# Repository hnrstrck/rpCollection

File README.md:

# rpCollection
Java-Objekte zum Anfassen am Raspberry Pi

## Beschreibung
Bei der Objektorientierten Modellierung (OOM) spielen Objekte eine fundamentale Rolle. Der klassische Ansatz im Unterricht arbeitet mit rein virtuellen Objekten - sämtliche Interaktion und auch die Objektkommunikation spielt sich im Rechner ab. Nicht selten kommt es dabei vor, dass man Objekte im wahrsten Sinne des Wortes gar nicht "sieht".

Ziel dieses Projektes ist es, Objekte begreifbar zu machen und Objektkommunikation zu visualisieren. Dafür stehen für den Unterricht Bauteile bereit, mit denen sich verschiedene Szenarien modellieren lassen. Die Schülerinnen und Schüler bekommen so die Möglichkeit, Objekte tatsächlich anzufassen und ihren aktuellen State (Zustand) nicht nur über Methoden zu erfragen, sondern auch zu *sehen* (Bauteil: RGB-LED) oder zu *hören* (Bauteil: Summer).

Auch die Kommunikation ist dabei dabei zu verfolgen. Die Idee ist im folgenden Bild veranschaulicht (pinke Kreise = am Raspberry Pi angeschlossene Bauteile (über Steckbrett), pinke Pfeile = Objektkommunikation).

<div align="center">

</div>

Die Umsetzung im Unterricht setzt auf Groovy (genauer: die Groovy-Console, aufzurufen über `groovyConsole`), in der sich mit korrekter Java-Syntax mit den Objekten praktisch arbeiten lässt (Objekte erstelen, Objekte modifizieren, Methoden aufrufen, Attribute abfragen etc.).

Es stehen folgende Bauteile (bzw. Objekte) bereit:

* Diode (LED)
* RGB-LED
* Phototransistor
* Taster
* AD-Wandler (für den Anschluss eines MCP3008- / MCP3208-Chips)
* Summer
* Motor (für den Anschluss eines Fischertechnik-Motors)

### Bilder
Im folgenden Bild ist eine angeschlossene RGB-LED zu erkennen. Die Kabel für Rot, Grün und Blau sind farblich abgestimmt, Schwarz ist für Ground (GND).

<div align="center" style="margin-top:20px;margin-bottom:20px">

</div>

Bilder sind auch im Ornder

    /Arbeitsblaetter/img/

zu sehen (Anschluss eines Helligkeitssensors, Diode und einer RGB-LED). Weitere Bilder folgen bei Gelegenheit.

<table style="width:100%">
  <tr>
    <td>
    
    <div align="center">LED</div>
    </td>
    <td>
    
    <div align="center">RGB-LED</div>
    </td>
    <td>
    
    <div align="center">Taster</div>
    </td>
  </tr>
  <tr>
    <td>
    <div align="center">Phototransistor</div>
    </td>
    <td>
    <div align="center">Summer</div>
    </td>
    <td>
    <div align="center">AD-Wandler (mit vier Reglern)</div>
    </td>
  </tr>
</table>

## Voraussetzungen
### Hardware
* Raspberry Pi
* GPIO
* Steckbrett
* Kabel zum Anschluss des GPIO an den Raspberry Pi (Flachbandkabel)
* Bauteile (Bauanleitungen und Bilder folgen)

### Software
* Pi4J ([Website](http://pi4j.com))
* WiringPi ([Website](http://wiringpi.com/))
* Groovy ([Website](http://groovy-lang.org/))
* Java

Die Installation kann wie folgt durchgeführt werden:

    sudo apt install openjdk-11-jdk wiringpi snapd
    wget https://pi4j.com/download/pi4j-1.4.deb
    sudo dpkg -i pi4j-1.4.deb

Nach einem Neustart des Raspberry Pi muss noch folgendes nachinstalliert werden:

    sudo snap install groovy --classic

#### Evtl. weitere Software
* LaTeX für den Etikettendruck (falls Bauteile nachgebaut werden sollen oder die Arbeitsblätter kompiliert werden sollen)
* KiCad zum Ausdrucken und Bearbeiten der Schaltpläne ([Website](http://kicad-pcb.org/))

## Anwendung und Beispiel

### Starten

Mit dem Aufruf

    bash start.sh

werden die Java-Dateien kompiliert und die Groovy-Console gestartet, sodass mit den Bauteilen gearbeitet werden kann. Die Pfade für Pi4J sind beim Aufruf bereits eingebunden.

### Beispiel
Durch die Eingaben

    meinLicht = new rpDiode()
    meinLicht.setPin(17)
    meinLicht.an()

wird eine an Pin 17 (BCM-Nummerierung) angeschlossene LED angeschaltet.

Für den Unterricht wurden extra Klassen erstellt, die der Modellierung aus dem Unterricht für das Theater-Arbeitsblatt entsprechen. Beispielsweise greift die Klasse `Scheinwerfer` auf die Klasse `rpDiode` zum Ansteuern einer LED zurück.

So ist es möglich, auf die im Unterricht getroffene Namensvergabe für die modellierten Objekte und Methoden einzugehen.

### Andere Startskripte

#### Groovy-Shell

    bash GSstart.sh

* Starte die Groovy-Shell (mit eingebundenen Pfaden für Pi4J)
* **kein** kompilieren der Java-Klassen (der Aufruf geht damit schneller)

bzw.

    bash GSstartC.sh

* Starte die Groovy-Shell (mit eingebundenen Pfaden für Pi4J)
* **kompilieren** der Java-Klassen
* dieses Skript entspricht dem Standard-Startskript `start.sh`

#### Groovy-Console

     bash GCstart.sh

* Starte die Groovy-Console (mit eingebundenen Pfaden für Pi4J)
* **kein** kompilieren der Java-Klassen (der Aufruf geht damit schneller)

bzw.

     bash GCstartC.sh

* Starte die Groovy-Console (mit eingebundenen Pfaden für Pi4J)
* **kompilieren** der Java-Klassen (der Aufruf geht damit schneller)

## Begleitung durch eine Masterarbeit

Die hier vorgestellten Materialien entstanden überwiegend im Rahmen einer Masterarbeit an der TU Dortmund. Weitere Informationen sind im Ordner

	/Masterarbeit_Heiner_Stroick

zu finden ([Direktlink](/Masterarbeit_Heiner_Stroick/Masterarbeit_Link.md)).

## Lizenz / License
Alle Dateien in diesem Repository steht unter einer *Namensnennung – Nicht-kommerziell – Weitergabe unter gleichen Bedingungen 4.0 International*-Lizenz (sofern nicht anders in der jeweiligen Datei angegeben). Die Bedingungen der Lizenz können unter folgendem Link eingesehen werden: [http://creativecommons.org/licenses/by-nc-sa/4.0/deed.de](http://creativecommons.org/licenses/by-nc-sa/4.0/deed.de)

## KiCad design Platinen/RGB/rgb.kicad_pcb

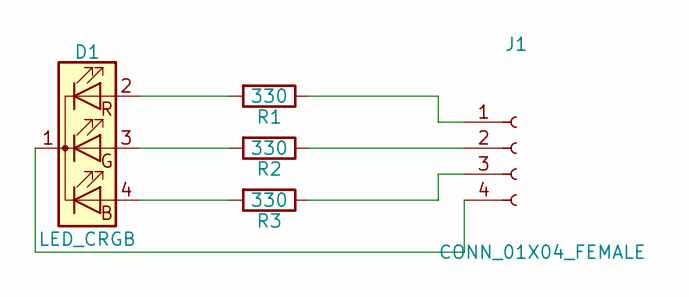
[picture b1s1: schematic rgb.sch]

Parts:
D1: LED_CRGB; LED_D5.0mm-4
J1: CONN_01X04_FEMALE; Pin_Header_Straight_1x04_Pitch2.54mm
R1, R2, R3: 330; R_Axial_DIN0207_L6.3mm_D2.5mm_P10.16mm_Horizontal

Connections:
unnamed: D1.1 (K), J1.4
unnamed: D1.2 (RA), R1.2
unnamed: D1.3 (GA), R2.2
unnamed: D1.4 (BA), R3.2
unnamed: J1.1, R1.1
unnamed: J1.2, R2.1
unnamed: J1.3, R3.1

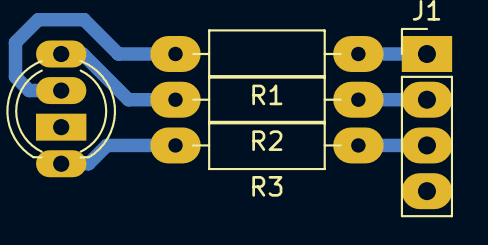
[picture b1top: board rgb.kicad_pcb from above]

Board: 2 copper layers, 5 parts (0 on the bottom side), 7 nets.

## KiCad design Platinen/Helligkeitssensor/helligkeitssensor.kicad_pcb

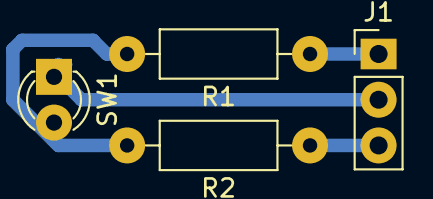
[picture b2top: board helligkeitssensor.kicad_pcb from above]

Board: 2 copper layers, 4 parts (0 on the bottom side), 4 nets.

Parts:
J1: CONN_01X03_FEMALE; PinHeader_1x03_P2.54mm_Vertical
R1: 1k; R_Axial_DIN0207_L6.3mm_D2.5mm_P10.16mm_Horizontal
R2: 10k; R_Axial_DIN0207_L6.3mm_D2.5mm_P10.16mm_Horizontal
SW1: SW_Push; LED_D3.0mm

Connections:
unnamed: J1.1, R1.1
unnamed: J1.2, SW1.1
unnamed: J1.3, R2.1
unnamed: R1.2, R2.2, SW1.2

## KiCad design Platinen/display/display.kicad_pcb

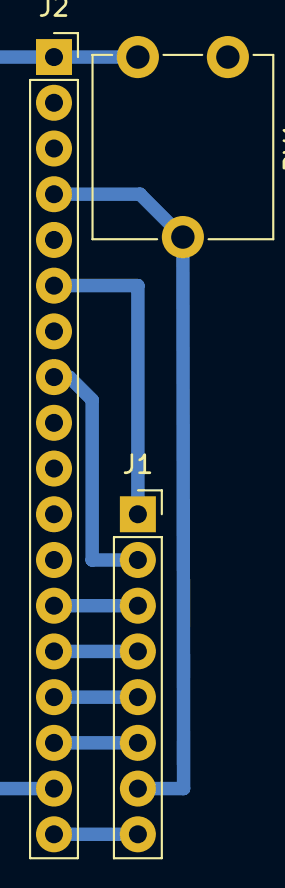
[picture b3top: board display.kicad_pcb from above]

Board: 2 copper layers, 3 parts (0 on the bottom side), 9 nets.

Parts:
J1: Conn_01x08_Female; PinSocket_1x08_P2.54mm_Vertical
J2: Conn_01x18_Female; PinSocket_1x18_P2.54mm_Vertical
RV1: R_POT; Potentiometer_ACP_CA9-V10_Vertical

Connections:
unnamed: J1.1, J2.6
unnamed: J1.2, J2.8
unnamed: J1.3, J2.13
unnamed: J1.4, J2.14
unnamed: J1.5, J2.15
unnamed: J1.6, J2.16
unnamed: J1.7, J2.4, RV1.2
unnamed: J1.8, J2.2, J2.3, J2.5, J2.7, J2.18
unnamed: J2.1, J2.17, RV1.1

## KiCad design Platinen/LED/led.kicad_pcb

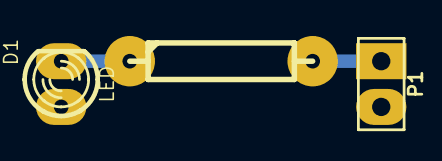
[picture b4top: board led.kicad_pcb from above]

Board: 2 copper layers, 3 parts (0 on the bottom side), 3 nets.

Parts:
D1: LED; LED-3MM
P1: CONN_2; PIN_ARRAY_2X1
R1: R; R4

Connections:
unnamed: D1.1, P1.2
unnamed: D1.2, R1.1
unnamed: P1.1, R1.2

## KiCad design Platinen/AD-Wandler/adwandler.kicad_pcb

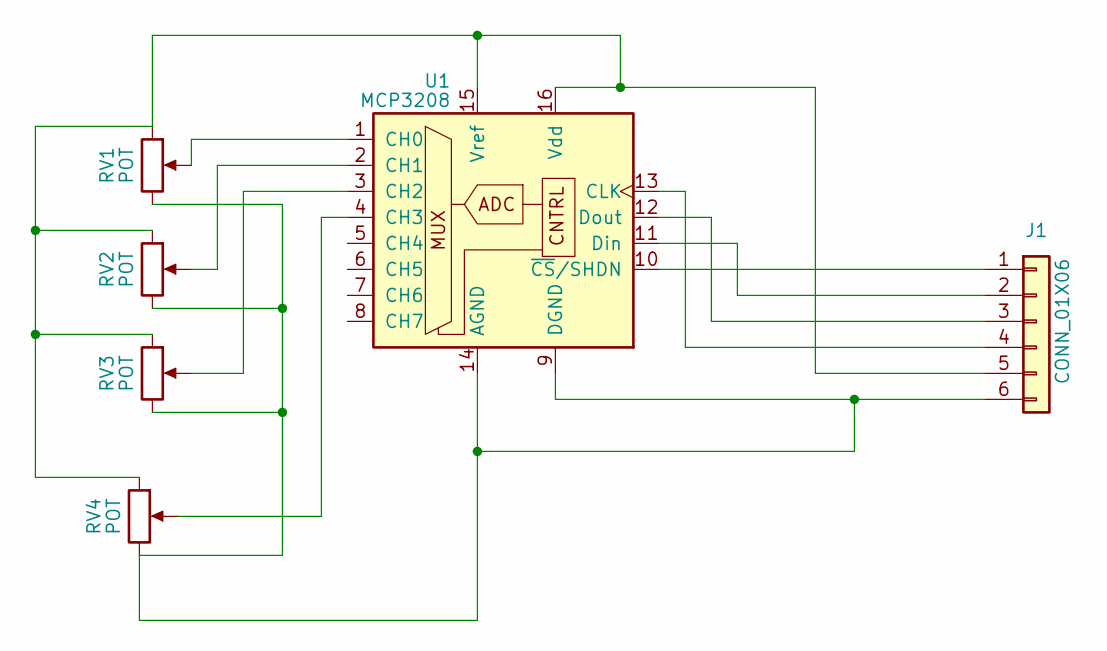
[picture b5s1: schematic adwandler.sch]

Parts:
J1: CONN_01X06; Socket_Strip_Straight_1x06_Pitch2.54mm_breit
RV1, RV2, RV3, RV4: POT; Potentiometer_Trimmer_ACP_CA9v_Horizontal_Px10.0mm_Py5.0mm_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
U1: MCP3208; DIP-16_W7.62mm_bigpads

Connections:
unnamed: J1.1, U1.10 (~CS~/SHDN)
unnamed: J1.2, U1.11 (Din)
unnamed: J1.3, U1.12 (Dout)
unnamed: J1.4, U1.13 (CLK)
unnamed: J1.5, RV1.1, RV2.1, RV3.1, RV4.1, U1.15 (Vref), U1.16 (Vdd)
unnamed: J1.6, RV1.3, RV2.3, RV3.3, RV4.3, U1.9 (DGND), U1.14 (AGND)
unnamed: RV1.2, U1.1 (CH0)
unnamed: RV2.2, U1.2 (CH1)
unnamed: RV3.2, U1.3 (CH2)
unnamed: RV4.2, U1.4 (CH3)

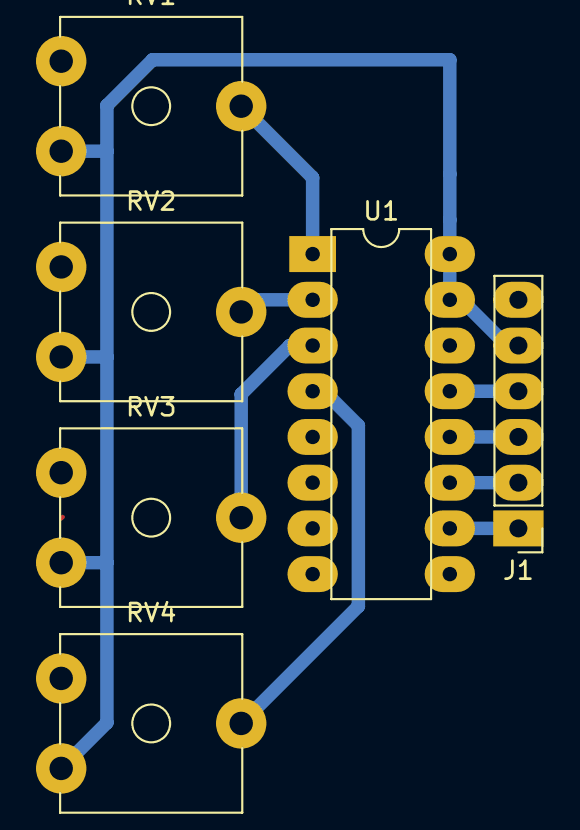
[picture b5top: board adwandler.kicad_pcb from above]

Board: 2 copper layers, 6 parts (0 on the bottom side), 10 nets.

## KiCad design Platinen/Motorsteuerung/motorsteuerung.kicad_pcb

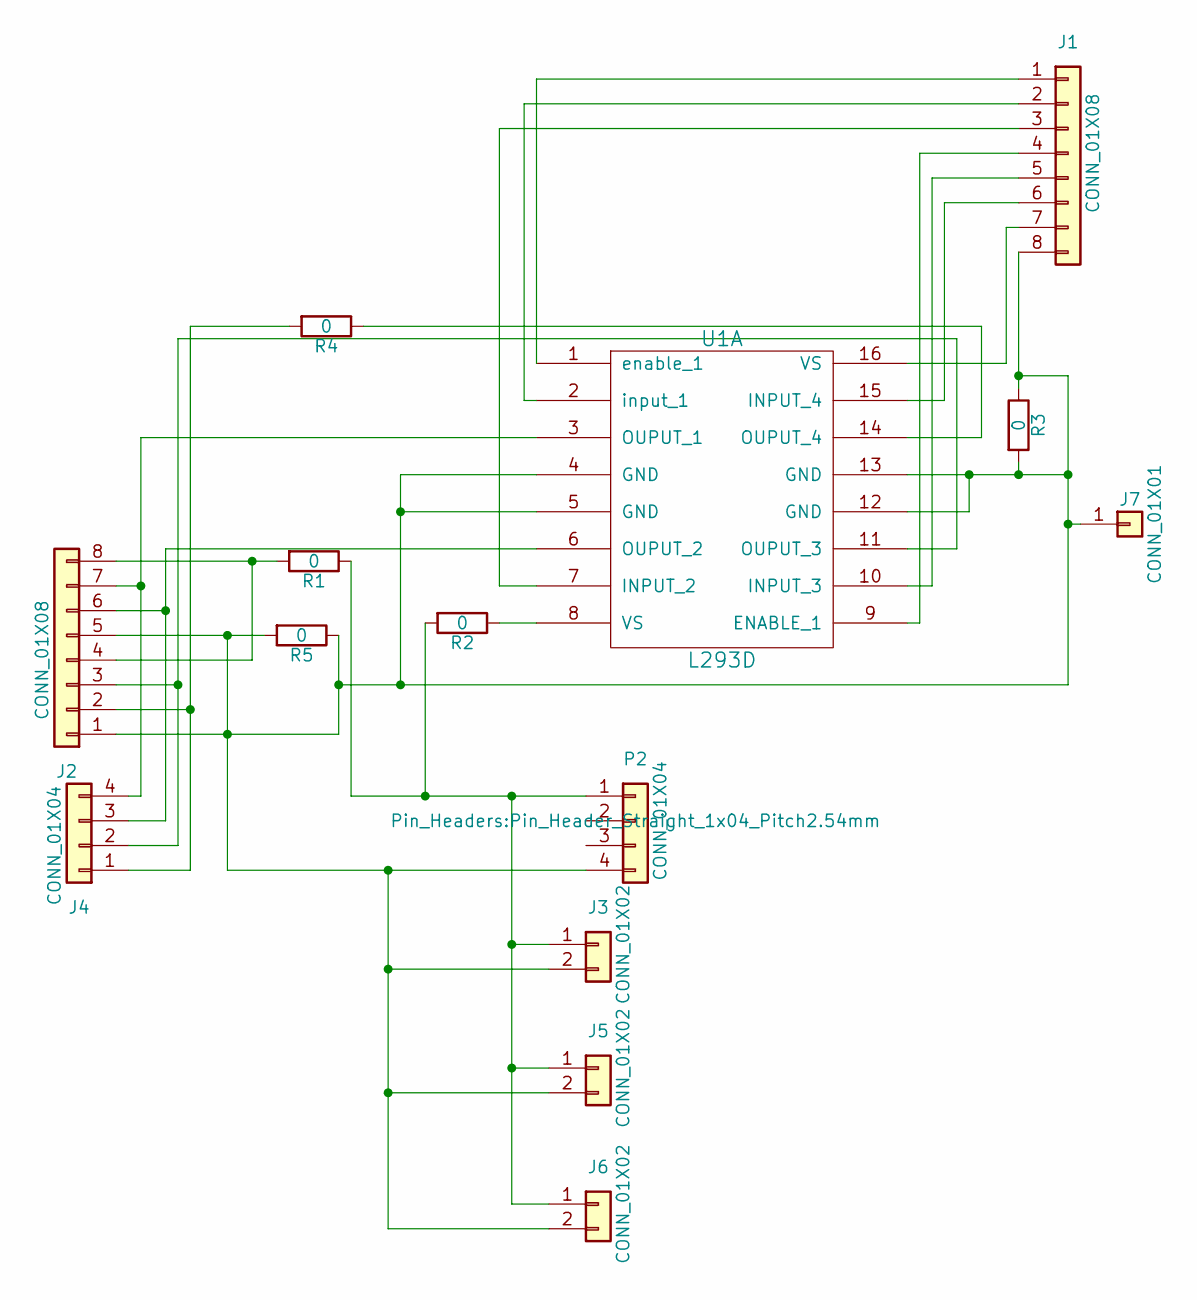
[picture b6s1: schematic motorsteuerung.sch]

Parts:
J1, J2: CONN_01X08; Pin_Header_Straight_1x08_Pitch2.54mm
J3: CONN_01X02; WAGO-233-2
J4: CONN_01X04; WAGO-233-4
J5, J6: CONN_01X02; Pin_Header_Straight_1x02_Pitch2.54mm
J7: CONN_01X01; Pin_Header_Straight_1x01_Pitch2.54mm
P2: CONN_01X04; Pin_Header_Straight_1x04_Pitch2.54mm
R1, R3, R4, R5: 0; R_Axial_DIN0204_L3.6mm_D1.6mm_P7.62mm_Horizontal
R2: 0; R_Axial_DIN0309_L9.0mm_D3.2mm_P20.32mm_Horizontal
U1: L293D; DIP-16_W7.62mm_LongPads

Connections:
unnamed: J1.1, U1.1 (enable_1)
unnamed: J1.2, U1.2 (input_1)
unnamed: J1.3, U1.7 (INPUT_2)
unnamed: J1.4, U1.9 (ENABLE_1)
unnamed: J1.5, U1.10 (INPUT_3)
unnamed: J1.6, U1.15 (INPUT_4)
unnamed: J1.7, U1.16 (VS)
unnamed: J1.8, J2.1, J2.5, J3.2, J5.2, J6.2, J7.1, P2.4, R3.1, R3.2, R5.1, R5.2, U1.4 (GND), U1.5 (GND), U1.12 (GND), U1.13 (GND)
unnamed: J2.2, J4.1, R4.2
unnamed: J2.3, J4.2, U1.11 (OUPUT_3)
unnamed: J2.4, J2.8, R1.2
unnamed: J2.6, J4.3, U1.6 (OUPUT_2)
unnamed: J2.7, J4.4, U1.3 (OUPUT_1)
unnamed: J3.1, J5.1, J6.1, P2.1, R1.1, R2.2
unnamed: R2.1, U1.8 (VS)
unnamed: R4.1, U1.14 (OUPUT_4)

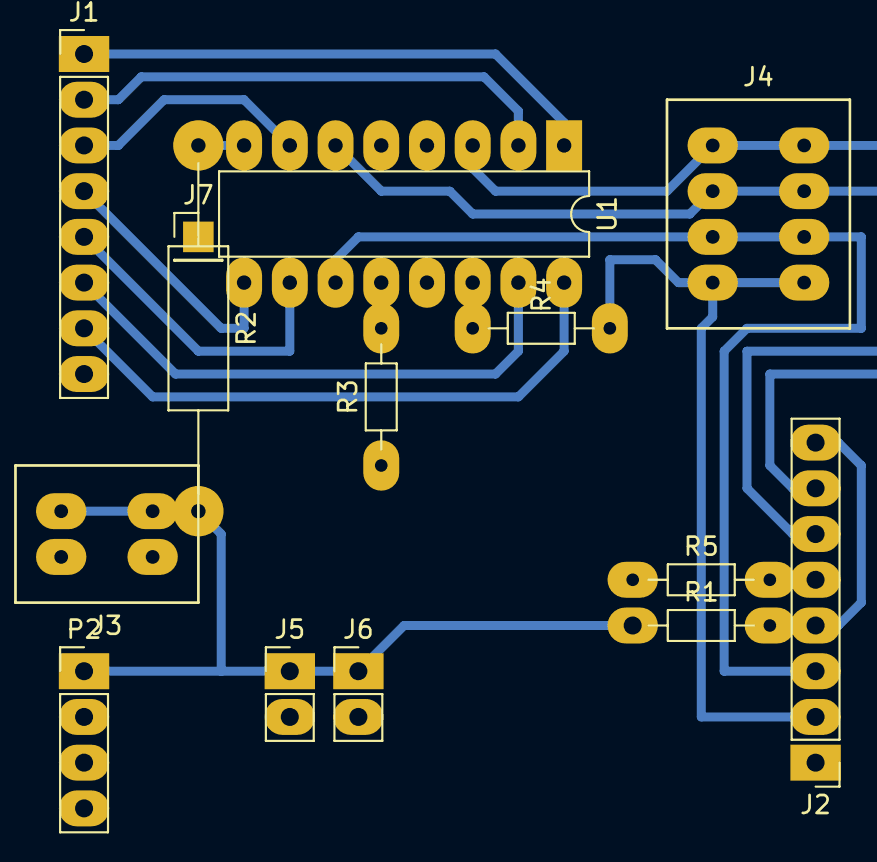
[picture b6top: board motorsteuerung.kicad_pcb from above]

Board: 2 copper layers, 14 parts (0 on the bottom side), 16 nets.

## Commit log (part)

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2016-09-11 Initialer Test
2016-09-11 Test hinzugefuegt
2016-09-11 Testing
2016-09-11 only testing
2016-09-11 Einstellen von rpDiode, rpPhototransistor, rpRGB
2016-09-12 CamelCase
2016-09-12 Anpassung GPIO
2016-09-12 Array fuer Pins pPin
2016-09-12 Anpassen von Array, setPin() jetzt mit Array, Testing, kleinere Fehlerbehebungen
2016-09-12 Anpassen von led.java
2016-09-12 Methoden rotAus(), gelbAus(), blauAus() hinzugefuegt
2016-09-13 java only
2016-09-13 Read me
2016-09-13 RGB Anpassung gelb -> gruen
2016-09-13 rpDiode hinzugefuegt
2016-09-13 Anpassungen RGB (Gelb -> Gruen) und Farbbereiche RGB 0...255
2016-09-14 Pulsweitenmodulation für RGB-Farbe hinzugefügt und gelb durch gruen ersetzt
2016-09-14 Einrückung korrigiert
2016-09-14 .DS_Store entfernt
2016-09-14 led_test.java entfernt - war nur fuer Testzwecke
2016-09-14 müssen -> muessen korrigiert
2016-09-16 main entfernt
2016-09-16 String Ueberwachung geaendert
2016-09-16 Initialer Commit des Tasters, rpTaster.java - noch nicht getestetgit add rpTaster.java
2016-09-20 Syntaxfehler korrigert in der Methode ueberwache10Mal()
2016-09-21 kleinere Korrekturen Einrückung
2016-09-22 AD-Wandler MCP3008 hinzugefuegt
2016-09-22 Methode destroy() hinzugefügt
2016-09-27 rpSummer fuer einen 3V Summer hinzugefuegt
2016-09-27 Attribute Reihenfolge geaendert
2016-10-11 Andern der Struktur; Startskript hinzugefuegt
2016-10-11 Aendern der Struktur
2016-10-11 Motor hinzugefuegt
2016-10-11 Abstaende
2016-10-13 Helferklasse fuer PIN-Belegung
2016-10-13 Zugriff erlaubt fuer rpDiode und rpRGB, Pin Belegung angepasst, zudem Einrükung angepasst
2016-10-13 Moeglichkeit eingebaut, Diode endlos blinken zu lassen und die Blinkfrequenz uber den Phototranistor zu steuern, zudem Pin Belegung über die Helferklasse angepasst und Einrückung formatiert.
2016-10-13 Etiketten für die Platinen hinzugefügt
2016-10-14 destroy() angepasst
2016-10-14 Unendliches Blinken angepasst
2016-10-14 Motor-Klasse hinzugefügt, mit der Möglichkeit den Motor in verschiedenen Stärken für ein paar Sekunden laufen zu lassen oder für unbestimmt lange Zeit, dabei Standardmethoden hinzugefügt.
2016-10-14 Überreste von der Klasse rpRGB.java entfernt
2016-10-14 Startskript nur fuer die Groovy-Shell (ohne die *.java-Dateien zu kompilieren)
2016-10-14 Weitere Etiketten hinzugefügt
2016-10-15 Methodensichtbarkeit geaendert und gibProzentwertVonChannel geaendert (Tippfehler)
2016-10-15 Weitere Etiketten für Bauteile hinzugefügt
2016-10-16 Pin-Layout BCM und J8 hinzugefuegt, ausserdem verwendet rpADWandler nun die eingestellte Aufloesung in der Helferklasse rpHelper. Ein Wechsel der Aufloesung und des Pin-Layouts ist moeglich.
2016-10-16 Verwendet nun das richtige Pin-Layout fuer die Pulsweitenmodulation (WiringPi)
2016-10-16 Verwendet nun das richtige Pin-Layout fuer die Pulsweitenmodulation (wie rpRGB)
2016-10-16 sleepMilliseconds(int milliseconds) auf private (statt public) gesetzt
2016-10-16 Thread-Sichtbarkeit auf prvate eingeschraenkt
2016-10-16 Javadoc hinzugefuegt fuer rpSummer, rpTaster
2016-10-16 destroy() geaendert
2016-10-16 Javadoc fuer rpHelper hinzugefuegt
2016-10-16 Leerzeichen entfernt bei der Berechnung in der Methode startBlinkenVariabel(...)
2016-10-16 Javadoc hinzugefuegt
2016-10-17 Fehlerbehebungen JavaDoc (HTML-Fehler, fehlende / ueberfluessige Parameter)
2016-10-17 Dokumentation hinzugefuegt (JavaDoc)
2016-10-17 Weitere Dateitypen ausschliessen
2016-10-17 Aufkleber / Etiketten Alternative hinzugefuegt
2016-10-17 Aufkleber / Etiketten - zwei Atlernativen
2016-10-17 Etiketten fuer die Hardwarebauteile der rpCollection
2016-10-17 Read Me für Github hinzugefügt
2016-10-19 Etikettendruck angepasst
2016-10-19 Einrückung geändet
2016-10-19 Arbeitsblätter für die Theateraufführung und den Kran hinzugefügt
2016-10-21 Änderung Encoding von AppleMac auf UTF8
2016-10-22 Neuer Text für Arbeitsauftrag zum Theater
2016-10-22 Klasse für die Regler am AD-Wandler
2016-10-22 Anpassungen, sodass jetzt auch die Klasse rpRegler verwendet wird und der MCP3208 korrekt ausgelesen wird
2016-10-22 Initiale Idee der Realisierung einer Ampel mit der rpCollection
2016-10-22 JavaDoc ergaenzt
2016-10-22 JavaDoc geandert
2016-10-22 Initialer Commit zur Idee der Klasse rpTheater.java
2016-10-22 Änderung Javadoc (Tippfehler)
2016-10-22 Startskript fuer den Mac ausgeschlossen
2016-10-22 Tippfehler JavaDoc berichtigt
2016-10-22 Beschreibung geändert
2016-10-22 Erklräung geändert bei der Ampelklasse
2016-10-22 Standard-Channel 0 raus genommen, damit es einen Fehler gibt, sollte ein nicht-vorhanener Channel eingestellt werden bei Objekterstellung
2016-10-24 Korrektur der Pin-Belegung für WiringPi
2016-10-24 Umbenennung Pins des Motors
2016-10-25 Variablenbenennung angepasst auf Etikett
2016-10-26 Änderung der Aufgabenstellung
2016-10-26 Änderungen Motor in die Doku aufgenommen
2016-10-28 Arbeitsblatt 2 Theater erstellt
2016-10-30 Änderungen Mac PI4J
2016-11-05 Klassen nach dem Objektspiel der SuS erstellt (Scheinwerfer, RGBScheinwerfer, Hintergrundbeleuchtung, Helligkeitssensor)
2016-11-05 Aktualisierung der Doku nach dem Objektspiel
2016-11-05 Ergänzung Aufruf + Bsp
2016-11-05 Quelltexte im Readme
2016-11-06 blinke() zum Scheinwerfer hinzugefuegt
2016-11-06 Änderungen Scheinwerfer.java und Aktualisierung der Doku
2016-11-11 Informationsblatt zum Anschliessen der Bauteile erstellt und Anpassungen in der style.tex vorgenommen (Quelltexte, etc.)
2016-11-11 Anpassung Überschrift
2016-11-17 Erweiterung um Kommentare im Quelltext
2016-11-17 schalten()-Methode hinzugefuegt bei Scheinwerfer, RGBScheinwerfer, rpDiode, rpRGB, rpSummer und Anpassung der Doku
2016-11-17 Bild ins README aufgenommen
2016-11-17 Bild ins README aufgenommen (Korrektur JPG-Bild, Änderung Größe)
2016-11-17 Dokument zum Anschluss der Bauteile um Bilder erweitert (Tabelle als Kommentar im tex-Dokument)
2016-11-17 Korrektur Referenz im Text auf die Bilder angepasst
2016-11-20 Änderung Überschrift
2016-11-22 Änderung der Methode zum Abfragen der Helligkeit (Helligkeitssensor) in befragenIstHell()
2016-11-22 Ausschluss Testprogramme
2016-11-22 Herunterfahren von Bauteilen implementiert, sodass Pins frei gegeben werden können (ehemals destroy() - jetzt herunterfahren() genannt)
2016-11-22 Anpassung der Doku (Erweiterung um die Methode herunterfahren() bei den Bauteilen
2016-11-22 Exception fuer doppelte Pin-Vergabe gefangen
2016-11-22 NullPointer-Exception gefangen, falls Pin bereits dereferenziert wurde
2016-11-22 Aktualisierung der Doku zwecks Änderungen in den Methoden zum herunterfahren der Bauteile
2016-11-22 Startskript für Groovy-Shell (mit Kompilieren)
2016-11-22 Startskript für Groovy-Shell (ohne Kompilieren)
2016-11-22 sudo beim Aufruf der Groovy-Console hinzugefügt
2016-11-22 Änderungen am Arbeitsblatt zum Anschluss der Bauteile vorgenommen (neue Struktur, Aufgabenstellung, Quelltext, wichtige Infos zum Anschluss)
2016-11-22 Vervollständigung der Quellen zum Auslesen des MCP3008, MCP3208
2016-11-23 Java-Fix-Skript für alte Pi Modelle
2016-11-23 Java-Fix vervollständigt
2016-11-23 Java-Fix vervollständigt (Ausgabe bei Beendigung)
2016-11-23 fix angepasst
2016-11-24 Befehl eingefügt zur Deinstallation von openjdk-7-jre-headless
2016-11-24 ReadMea auf Groovy-Console angepasst, weitere Erklärungen ergänzt
2016-11-24 Absatz eingefügt
2016-11-24 Markdown Quelltext-Highlight korrigiert
2016-11-24 Verweis auf start.sh eingefügt
2016-11-24 Rechtschreibfehler in den Kommentaren behoben
2016-11-25 Doppeltes Asterik entfernt
2016-11-25 Lizenz hinzugefügt
2016-11-25 Tabelle mit Bildern der Bauteilen ergänzt
2016-11-25 Hinweis Regler im Readme ergänzt
2016-11-25 Hinweis Regler im Readme ergänzt (Korrektur)
2016-11-26 Ausschluss privates Startskript
2016-11-26 rpHelper in Helfer umbenannt (Grossbuchstabe zu Beginn, damit der Aufruf statischer Methoden in Groovy klappt). Aenderung des Klassennamen in anderen Klassen uebernommen. Moeglichkeit eingebaut, den 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
2016-11-26 Einrueckung angepasst
2016-11-26 Generatorskript fuer die JavaDoc
2016-11-26 Anpassungen JavaDoc
2016-11-26 Update JavaDoc
2016-11-27 Aenderung Text JavaDoc
2016-11-27 Update JavaDoc fuer Helfer
2016-11-28 Alte Dateien entfernt
2016-11-28 Update Java-Doc
2016-11-30 Objekte herunterfahren erweiteret, Größe der Bilder angepasst
2016-12-12 Textänderung 2 AB2 - Theater
2016-12-13 Klasse Taster hinzugefuegt
2016-12-13 Buehne hinzugefuegt
2016-12-13 Moeglichkeit eingebaut, dass die Hintergrundbeleuchtung den Helligkeitssensor kennen kann.
2016-12-13 Helfer geaendert, dass die Methode freigeben() jetzt auch den GPIO herunter faehrt
2016-12-13 Ueberarbeitete Doku
2016-12-19 Infoblatt Beziehungen Hintergrundbeleuchtung und Helligkeitssensor
2016-12-20 Update Text Infoblatt Beziehungen
2016-12-20 Update Pfeile
2016-12-21 Typo korrigiert
2016-12-21 Text eingefuegt beim Setzten des Helligkeitssensors (Info Shell)
2017-01-06 Umbenennung der Klassen
2017-01-06 Großschreibung der Klassen
2017-01-06 Anpassung Groß- u. Kleinschreibung
2017-01-06 Update Doku
2017-01-09 Update Kran-Arbeitsblatt
2017-01-09 Update Doku (saubere Dokumenation erzeugt)
2017-01-21 Update Struktur ABs
2017-01-28 Update Blatt 2 (Theater)
2017-01-30 Hinweis zum Ausschalten des Lichts eingefügt (am Ende des Textes)
2017-02-26 Infoblatt zu Klassen und Klasse Mischpult
2017-02-27 Fehler im Arbeitsblatt behoben
2017-04-02 Platinenvorlagen hinzugefügt
2017-04-07 Update Semikolae bei einfachen groovy-Eingaben
2017-04-07 Informatik-Tag 2017 Wuppertal: Materialien (Präsentation, Arbeitsblatt) eingefügt
2017-04-22 Hinweis Software + Masterarbeit eingefügt
2017-04-22 Hinweise zur Java-Installation eingefügt
2017-04-22 Repo-Link ausgeschrieben und Hinweis auf 'git clone' gegeben
2017-08-18 Update Java-Installationshinweise
2017-12-25 Platinen aktuallisiert nach Ätzen der ersten Prototypplatine
2018-01-10 Klassen für neue Anforderungen erweitert
2018-04-15 Zwei Infoblätter hinzugefügt
2018-04-17 Update theater_bauteile_anschliessen.tex
    Dateiendungen hinzugefügt für die Bilder
2018-09-27 Klasse für ein Display über I2C hinzugefügt
2018-09-30 Klassendiagramm überarbeitet
2018-12-05 Starten von Groovy direkt
2018-12-07 Schaltpläne überarbeitet
2018-12-08 Displayklassen ergänzt und ausgebessert
2018-12-10 Anpassung an neue Modellierung
2018-12-10 Schweinwerfer schalten verbessert
2018-12-10 Etiketten für RFID
2019-06-03 In Helfer ein schaltbares println eingefügt und in einzelnen Klassen übernommen
2019-12-10 Platinen überarbeitet
2019-12-11 Helligkeitssensor als Platine hinzugefügt
2019-12-28 Platinen auf den neusten Stand gebracht und alternatives Layout bei der LED
2020-01-07 Änderungen für Raspi 4
2020-11-26 Alternative zur Fortsetzung. AB zum Helligkeitssensor nachgebessert
2020-12-04 Klassen für den zweiten Akt
2020-12-04 gitignore erweitert
2021-08-24 Startscripte ausgebessert
2021-08-31 Anpassung README an aktuell Bedingungen bzgl. der Software
2021-08-31 Hinweise auf nicht mehr nötigen Fix für Java entfernt
2021-09-04 Dummyklassen für die Benutzung ohne Raspberry Pi hinzugefügt
2021-11-09 Update README.md
    https://forum.kicad.info/t/warning-avoid-all-links-to-kicad-pcb-org-use-kicad-org/31521
2022-04-04 RPTastenfeld
2022-04-04 Dokumentation mit neuen Skript neu generiert
2022-04-04 Dokumentation nochmal angepasst
2022-04-06 Dokumentation Finalement
2022-04-06 Tabs und Spaces zu nur Spaces
2022-04-06 logs angepasst
2022-11-13 Erste Klassen auf pi4j v2 umzustellen
2022-11-20 Weitere Elemente auf Pi4j v2.0 umgestellt
2023-03-30 Tastenfeld auf pi4j v2 umgebaut
2023-04-01 Motor, ADWandler und I2C-Display auf pi4j v2 umgestellt
2023-04-01 Display und RFID auf pi4j v2 umgestellt
2023-04-01 ServoMotor mit hinzugefügt
2023-05-21 Anpassungen der Dokumentation der Klassen und Erzeugung der JavaDoc per Script
2023-05-21 JavaDoc aktuallisiert
2025-01-09 Anpassungen an Neuerungen in pi4j
2025-01-16 Anpassungen für RGB-Diode und Script
2025-02-02 Anpassungen an Testkonfiguration
2025-02-02 Nachbesserungen zum Testen
2025-02-09 Abstandssensor ergänzt und Pins zum Testen geändert
2025-02-11 Schrittmotor hinzugefügt und Testelemente korrigiert
